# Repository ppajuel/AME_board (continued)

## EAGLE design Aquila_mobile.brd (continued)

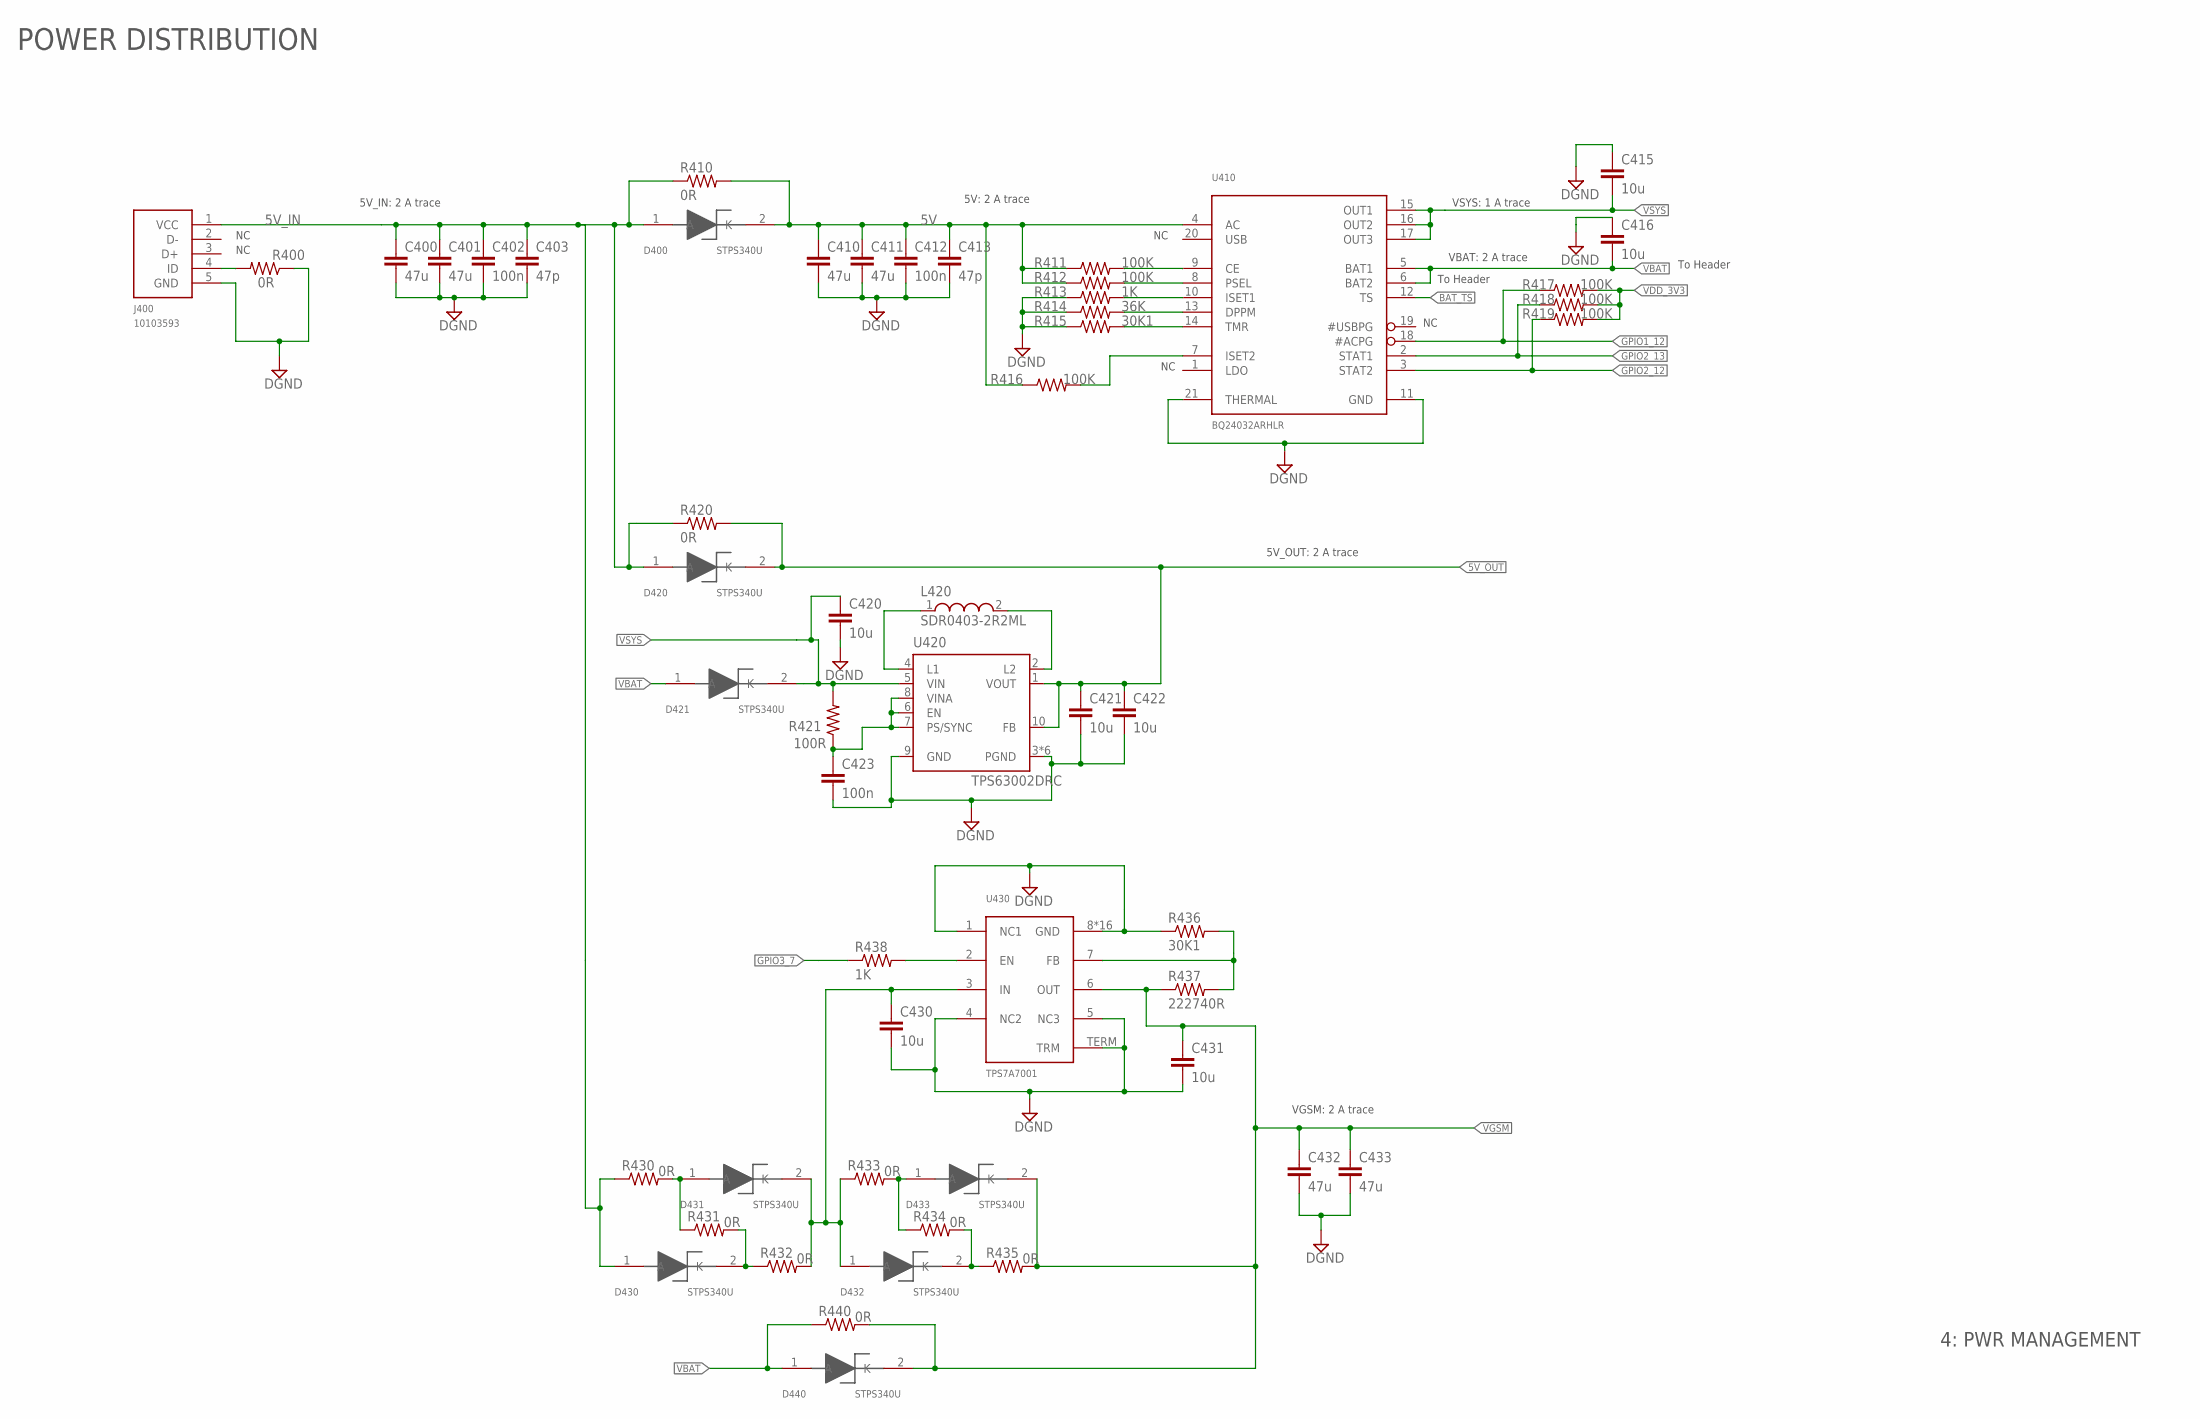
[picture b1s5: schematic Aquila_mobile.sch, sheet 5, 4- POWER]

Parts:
C400, C401, C410, C411, C432, C433: 47u; C0805
C402, C412, C423: 100n; C0603
C403, C413: 47p; C0603
C415, C416, C420, C421, C422, C430, C431: 10u; C0603
D400, D420, D421, D430, D431, D432, D433, D440: STPS340U; SMB
J400: 10103593; 10103593-0001LF
L420: SDR0403-2R2ML; SDR0403
R400, R410, R420, R430, R431, R432, R433, R434, R435, R440: 0R; R0402
R411, R412, R416, R417, R418, R419: 100K; R0603
R413, R438: 1K; R0603
R414: 36K; R0603
R415, R436: 30K1; R0603
R421: 100R; R0603
R437: 222740R; R0603
U410: BQ24032ARHLR
U420: TPS63002DRC; DRC-S-PVSON-N10
U430: TPS7A7001; 8SO_POWERPAD

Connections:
5V: C410.1, C411.1, C412.1, C413.1, D400.2 (K), R410.2, R411.1, R412.1, R416.1, U410.4 (AC)
5V_IN: C400.1, C401.1, C402.1, C403.1, D400.1 (A), D420.1 (A), D430.1 (A), J400.1 (VCC), R410.1, R420.1, R430.1; also elsewhere on the board
5V_OUT: C421.1, C422.1, D420.2 (K), R420.2, U420.1 (VOUT), U420.10 (FB); also elsewhere on the board
BAT_TS: U410.12 (TS); also elsewhere on the board
DGND: C400.2, C401.2, C402.2, C403.2, C410.2, C411.2, C412.2, C413.2, C415.1, C416.1, C420.2, C421.2, C422.2, C423.2, C430.2, C431.2, C432.2, C433.2, J400.5 (GND), R400.1, R413.1, R414.1, R415.1, R436.1, U410.11 (GND), U410.21 (THERMAL), U420.3 (PGND), U420.9 (GND), U420.EXP@1 (PGND), U420.EXP@2 (PGND), U420.EXP@3 (PGND), U420.EXP@4 (PGND), U420.TH (PGND), U430.1 (NC1), U430.4 (NC2), U430.5 (NC3), U430.8 (GND), U430.EXP@1 (GND), U430.EXP@2 (GND), U430.EXP@6 (GND), U430.EXP@7 (GND), U430.EXP@8 (GND), U430.EXP@9 (GND), U430.EXP@10 (GND), U430.EXP@11 (GND), U430.EXP@14 (GND), U430.EXP@15 (GND), U430.EXP@16 (GND), U430.EXP@17 (GND), U430.EXP@18 (GND), U430.EXP@24 (GND), U430.EXP@25 (GND), U430.TERM (TRM); also elsewhere on the board
GPIO1_12: R417.1, U410.18 (#ACPG); also elsewhere on the board
GPIO2_12: R419.1, U410.3 (STAT2); also elsewhere on the board
GPIO2_13: R418.1, U410.2 (STAT1); also elsewhere on the board
GPIO3_7: R438.1; also elsewhere on the board
unnamed: D431.1 (A), R430.2, R431.1
unnamed: R411.2, U410.9 (CE)
unnamed: J400.4 (ID), R400.2
unnamed: R412.2, U410.8 (PSEL)
unnamed: R413.2, U410.10 (ISET1)
unnamed: R414.2, U410.13 (DPPM)
unnamed: R415.2, U410.14 (TMR)
unnamed: R416.2, U410.7 (ISET2)
unnamed: L420.1, U420.4 (L1)
unnamed: L420.2, U420.2 (L2)
unnamed: D430.2 (K), R431.2, R432.1
unnamed: C423.1, R421.1, U420.6 (EN), U420.7 (PS/SYNC), U420.8 (VINA)
unnamed: D433.1 (A), R433.2, R434.1
unnamed: D432.2 (K), R434.2, R435.1
unnamed: R436.2, R437.2, U430.7 (FB)
unnamed: C430.1, D431.2 (K), D432.1 (A), R432.2, R433.1, U430.3 (IN)
unnamed: R438.2, U430.2 (EN)
VBAT: C416.2, D421.1 (A), D440.1 (A), R440.1, U410.5 (BAT1), U410.6 (BAT2); also elsewhere on the board
VDD_3V3: R417.2, R418.2, R419.2; also elsewhere on the board
VGSM: C431.1, C432.1, C433.1, D433.2 (K), D440.2 (K), R435.2, R437.1, R440.2, U430.6 (OUT); also elsewhere on the board
VSYS: C415.2, C420.1, D421.2 (K), R421.2, U410.15 (OUT1), U410.16 (OUT2), U410.17 (OUT3), U420.5 (VIN)

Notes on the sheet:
POWER DISTRIBUTION
5V_IN: 2 A trace
To Header
VGSM: 2 A trace
5V_OUT: 2 A trace
VBAT: 2 A trace
VSYS: 1 A trace
5V: 2 A trace
4: PWR MANAGEMENT

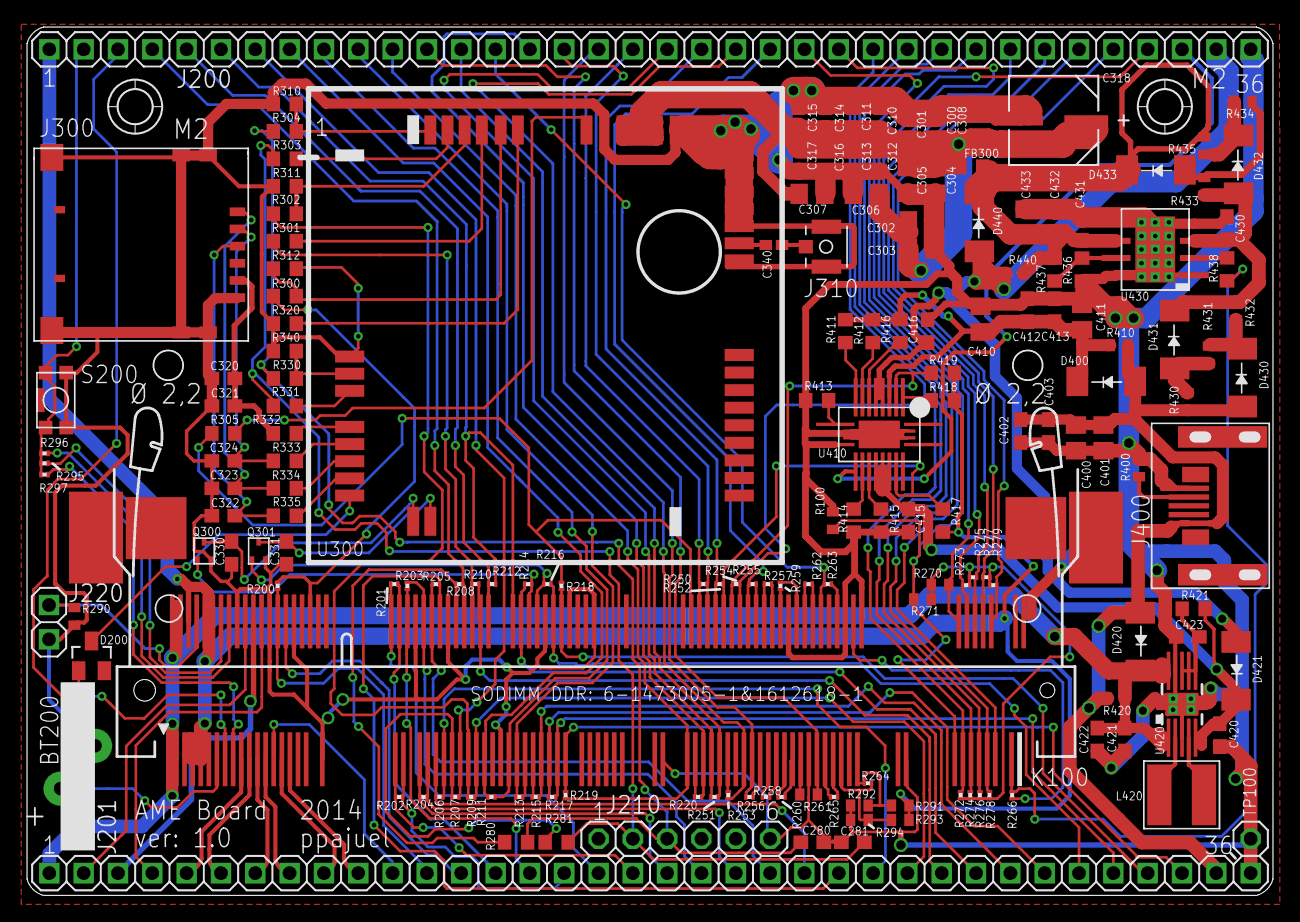
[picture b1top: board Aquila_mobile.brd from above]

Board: 2 copper layers, 91.4 x 63.4 mm, 177 parts (0 on the bottom side), 157 nets.

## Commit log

2017-05-21 README.md: Update information
2017-05-21 First schematic and layout release
    sch and brd files contain Eagle schematic and layout respectively
2017-05-21 Add gerbers for release one
2017-05-21 Add schematic pdf for release one
2017-06-04 Layout: fix errata into U410 and U420 pads
    Pads from U410 and U420 designators didn't contain solder mask (tStop)
    and stencil mask (tCream). This patch corrects designs files and gerbers.
2017-06-04 CAM: Add LaenPCBOrder CAM job
    This CAM job script has been verified with the first prototipes
